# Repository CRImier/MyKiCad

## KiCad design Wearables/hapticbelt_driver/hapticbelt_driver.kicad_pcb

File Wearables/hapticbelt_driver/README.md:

# Haptic belt driver

This board uses WS2818B chips and P-FETs to drive vibromotors with PWM, 3 per board.
It uses 4-pin 0.5mm FPC connectors for power and wiring, with backup 1mm pads on the back.
The 2818 chip has a redundant signal input, but the board can surely be driven without it.

This is for a "simple DIY haptic belt" project.. hopefully it helps others as well!

## Notes

- Signal names are silkscreened on the board's bottom layers.
- This board is untested and there's no guarantees of fitness.
- I recommend a stencil for assembling this board.

## Info

- Software: Kicad 7
- Version: 1
- PCB size: 17x17mm
- Layer count: 2

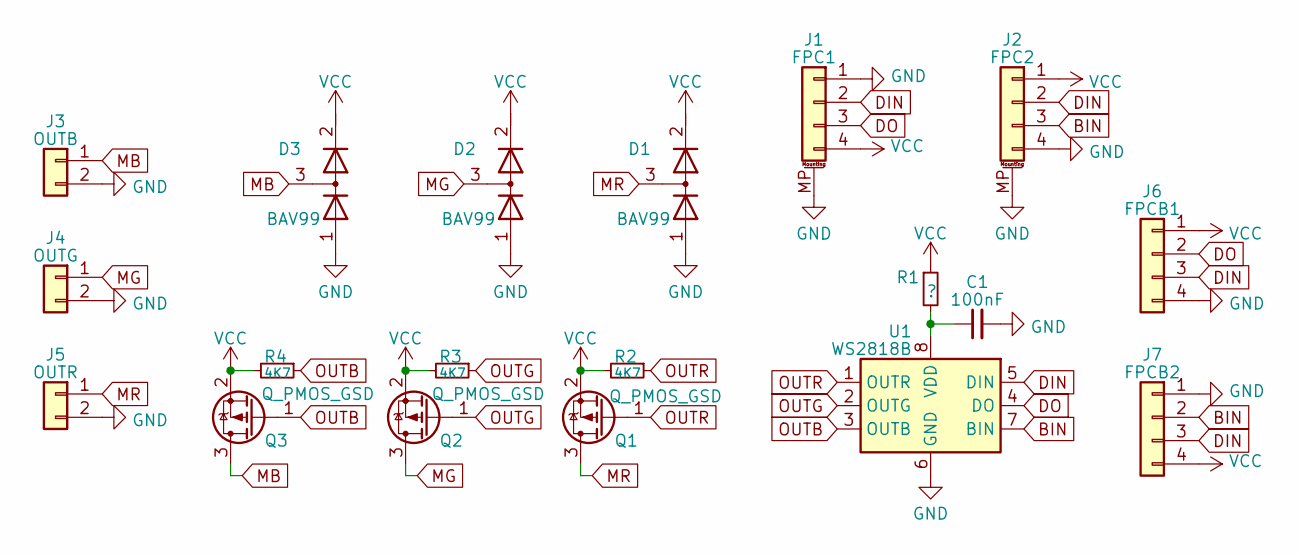
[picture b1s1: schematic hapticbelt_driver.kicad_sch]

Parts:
C1: 100nF; C_0603_1608Metric
D1, D2, D3: BAV99; SOT-23
J1: FPC1; FPC_4
J2: FPC2; FPC_4
J3: OUTB; PinHeader_1x02_P2.00mm_Vertical
J4: OUTG; PinHeader_1x02_P2.00mm_Vertical
J5: OUTR; PinHeader_1x02_P2.00mm_Vertical
J6: FPCB1; FPC_4_1mm
J7: FPCB2; FPC_4_1mm
Q1, Q2, Q3: Q_PMOS_GSD; SOT-23
R1: ?; R_0603_1608Metric
R2, R3, R4: 4K7; R_0603_1608Metric
U1: WS2818B; SOP-8_3.9x4.9mm_P1.27mm

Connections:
BIN: J2.3, J7.2, U1.7 (BIN)
DIN: J1.2, J2.2, J6.3, J7.3, U1.5 (DIN)
DO: J1.3, J6.2, U1.4 (DO)
GND: C1.2, D1.1 (A), D2.1 (A), D3.1 (A), J1.1, J1.MP (MountPin), J2.4, J2.MP (MountPin), J3.2, J4.2, J5.2, J6.4, J7.1, U1.6 (GND)
MB: D3.3 (common), J3.1, Q3.3 (D)
MG: D2.3 (common), J4.1, Q2.3 (D)
MR: D1.3 (common), J5.1, Q1.3 (D)
unnamed: C1.1, R1.2, U1.8 (VDD)
OUTB: Q3.1 (G), R4.1, U1.3 (OUTB)
OUTG: Q2.1 (G), R3.1, U1.2 (OUTG)
OUTR: Q1.1 (G), R2.1, U1.1 (OUTR)
VCC: D1.2 (K), D2.2 (K), D3.2 (K), J1.4, J2.1, J6.1, J7.4, Q1.2 (S), Q2.2 (S), Q3.2 (S), R1.1, R2.2, R3.2, R4.2

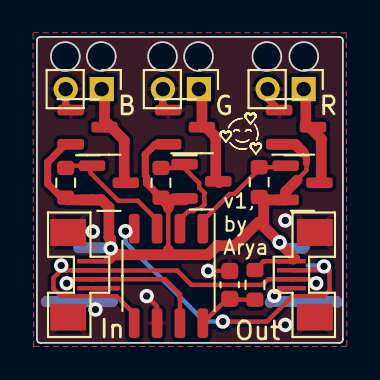
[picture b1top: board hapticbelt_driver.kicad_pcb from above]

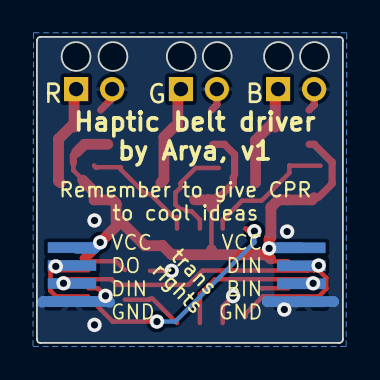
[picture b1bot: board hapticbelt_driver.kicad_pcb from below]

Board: 2 copper layers, 17.0 x 17.0 mm, 19 parts (2 on the bottom side), 12 nets.
